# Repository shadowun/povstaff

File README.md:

# POV staff
This repository contains all files related to Persistence of Vision (POV) staff
project. A detailed write-up of this project is available on  Instructables at
[https://www.instructables.com/Persistence-of-Vision-LED-Staff/](https://www.instructables.com/Persistence-of-Vision-LED-Staff/);
you can also find there photos  of the staff in action.

A guide for using the assembled staff and uploading images to it is available
in directory `docs`; see file USER_GUIDE.md and USER_GUIDE.pdf for PDF version.

## Structure of this repository  
This repository is organized as follows:

* `binaries`: pre-complied binaries
* `docs`: documentation
* `hardware`:  design files for the custom PCBs used in
  the project, as well as STEP files for the 3d printed components.
* `images`: sample image(s) and  `imagelist.txt` file

## Authors and license
This project was created by Alexander Kirillov <shurik179@gmail.com>; it is
based on [earlier work](https://learn.adafruit.com/pov-dotstar-double-staff) of
Phillip Burgess and Erin St Blaine from Adafruit. The project is available under
MIT license; see LICENSE file for details.

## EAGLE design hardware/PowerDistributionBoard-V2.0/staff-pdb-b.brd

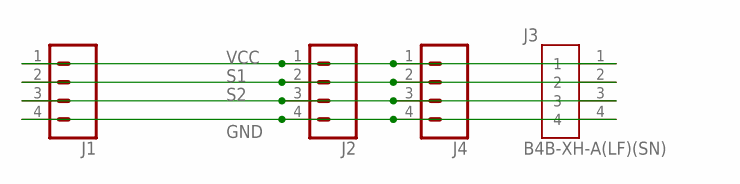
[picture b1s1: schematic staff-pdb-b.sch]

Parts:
J1, J2, J4: CONN_04; 1X04
J3: B4B-XH-A(LF)(SN); JST_B4B-XH-A(LF)(SN)

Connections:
GND: J1.4, J2.4, J3.4, J4.4
S1: J1.2, J2.2, J3.2, J4.2
S2: J1.3, J2.3, J3.3, J4.3
VCC: J1.1, J2.1, J3.1, J4.1

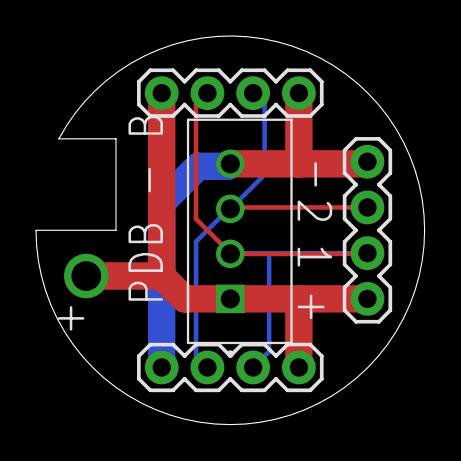
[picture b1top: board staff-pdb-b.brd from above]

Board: 2 copper layers, 21.6 x 21.6 mm, 4 parts (0 on the bottom side), 4 nets.

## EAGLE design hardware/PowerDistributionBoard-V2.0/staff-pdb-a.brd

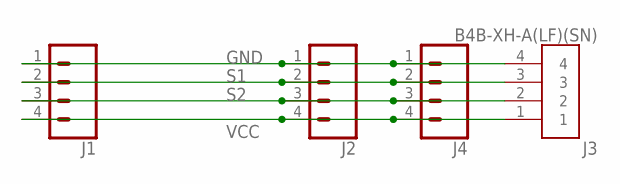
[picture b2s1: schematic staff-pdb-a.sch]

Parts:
J1, J2, J4: CONN_04; 1X04
J3: B4B-XH-A(LF)(SN); JST_B4B-XH-A(LF)(SN)

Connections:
GND: J1.1, J2.1, J3.4, J4.1
S1: J1.2, J2.2, J3.3, J4.2
S2: J1.3, J2.3, J3.2, J4.3
VCC: J1.4, J2.4, J3.1, J4.4

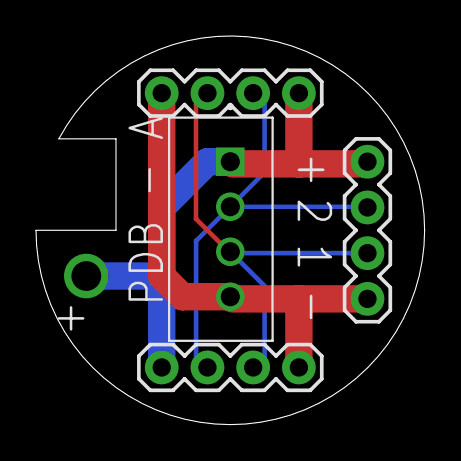
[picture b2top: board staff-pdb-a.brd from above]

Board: 2 copper layers, 21.6 x 21.6 mm, 4 parts (0 on the bottom side), 4 nets.

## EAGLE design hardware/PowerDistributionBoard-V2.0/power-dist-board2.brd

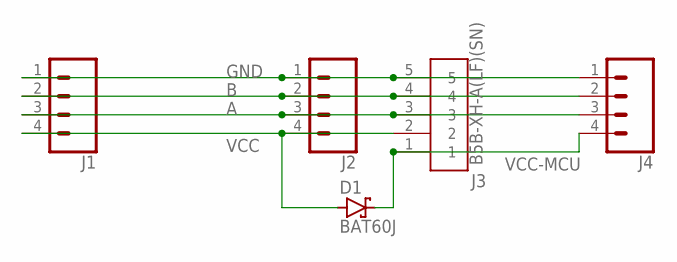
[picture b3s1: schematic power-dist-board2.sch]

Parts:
D1: BAT60J; SOD323_ST
J1, J2, J4: CONN_04; 1X04
J3: B5B-XH-A(LF)(SN); JST_B5B-XH-A(LF)(SN)

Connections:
A: J1.3, J2.3, J3.3, J4.3
B: J1.2, J2.2, J3.4, J4.2
GND: J1.1, J2.1, J3.5, J4.1
VCC: D1.A, J1.4, J2.4, J3.2
VCC-MCU: D1.C, J3.1, J4.4

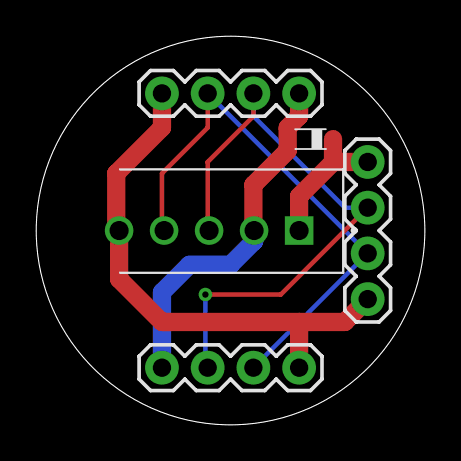
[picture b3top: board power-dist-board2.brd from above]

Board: 2 copper layers, 21.6 x 21.6 mm, 5 parts (0 on the bottom side), 5 nets.

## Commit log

2021-10-19 updating boards
2021-10-19 deleting code
    Will be moved to a repo of its own
2021-10-20 rearranging files
2021-10-20 fixing typo in conf.py
2021-10-20 docs outline
2021-10-20 docs update
2021-10-26 doc update
